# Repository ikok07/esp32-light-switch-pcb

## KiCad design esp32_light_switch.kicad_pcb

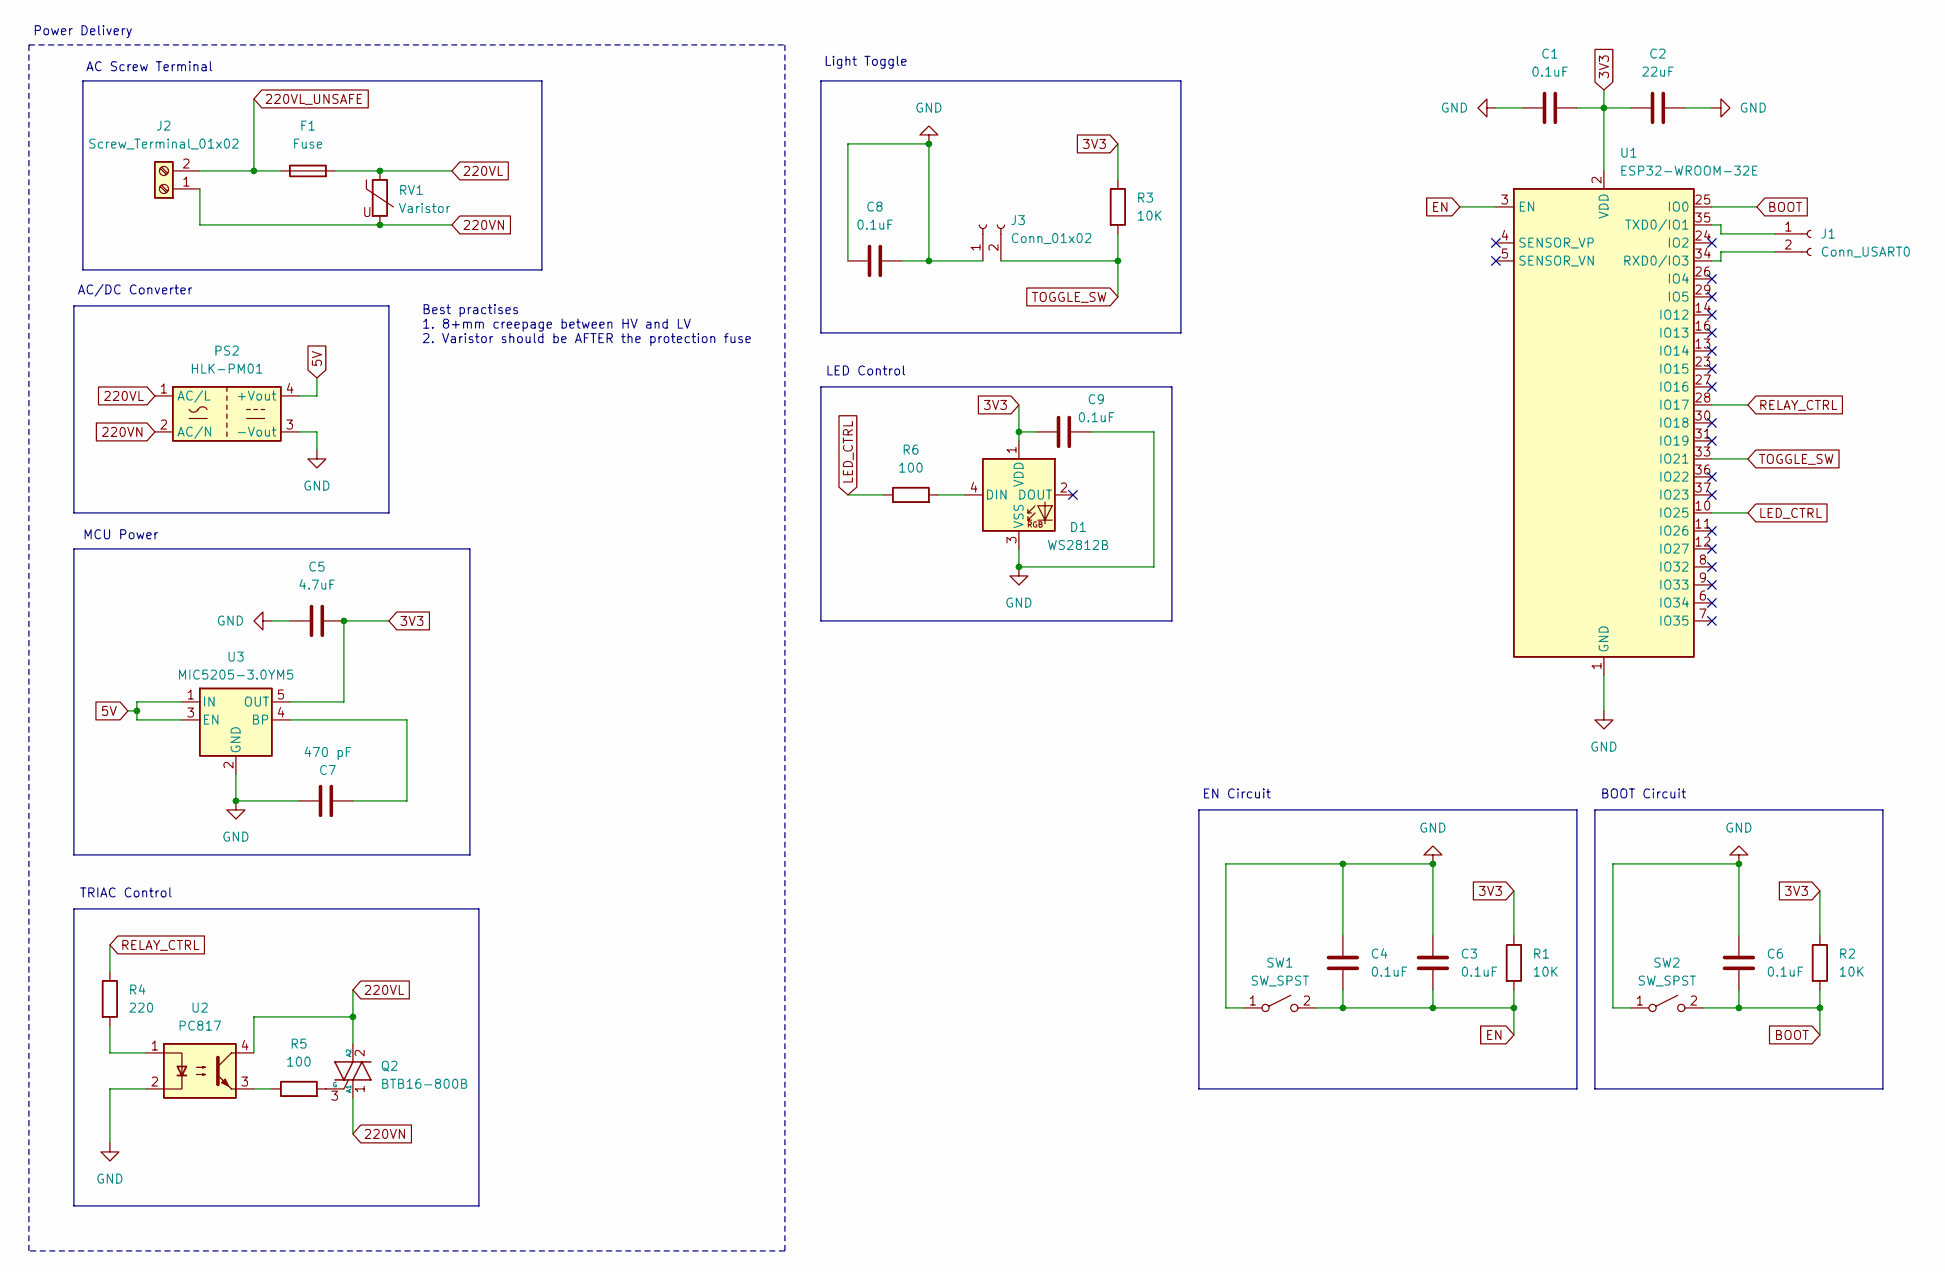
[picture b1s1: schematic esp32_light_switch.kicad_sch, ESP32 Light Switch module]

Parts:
C1, C3, C4, C6, C8, C9: 0.1uF; C_0805_2012Metric_Pad1.18x1.45mm_HandSolder
C2: 22uF; C_0805_2012Metric_Pad1.18x1.45mm_HandSolder
C5: 4.7uF; CP_EIA-6032-20_AVX-F_HandSolder
C7: 470 pF; C_Disc_D5.0mm_W2.5mm_P5.00mm
D1: WS2812B; LED_WS2812B_PLCC4_5.0x5.0mm_P3.2mm
F1: Fuse; Fuseholder_Cylinder-5x20mm_Schurter_0031_8201_Horizontal_Op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
J1: Conn_USART0; PinHeader_1x02_P2.54mm_Vertical
J2: Screw_Terminal_01x02; DG3065002P1200AH
J3: Conn_01x02; PinHeader_1x02_P2.54mm_Vertical
PS2: HLK-PM01; Converter_ACDC_Hi-Link_HLK-PMxx
Q2: BTB16-800B; TO-220-3_Vertical
R1, R2, R3: 10K; R_0805_2012Metric_Pad1.20x1.40mm_HandSolder
R4: 220; R_0805_2012Metric_Pad1.20x1.40mm_HandSolder
R5, R6: 100; R_0805_2012Metric_Pad1.20x1.40mm_HandSolder
RV1: Varistor; RV_Disc_D12mm_W3.9mm_P7.5mm
SW1, SW2: SW_SPST; SW_TH_Tactile_Omron_B3F-100x
U1: ESP32-WROOM-32E; ESP32-WROOM-32D
U2: PC817; DIP-4_W7.62mm_SMDSocket_SmallPads
U3: MIC5205-3.0YM5; SOT-23-5

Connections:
3V3: C1.2, C2.1, C5.2, C9.1, D1.1 (VDD), R1.1, R2.1, R3.1, U1.2 (VDD), U3.5 (OUT)
5V: PS2.4 (+Vout), U3.1 (IN), U3.3 (EN)
220VL: F1.2, PS2.1 (AC/L), Q2.2 (A2), RV1.1, U2.4
220VL_UNSAFE: F1.1, J2.2
220VN: J2.1, PS2.2 (AC/N), Q2.1 (A1), RV1.2
BOOT: C6.1, R2.2, SW2.2 (B), U1.25 (IO0)
EN: C3.1, C4.2, R1.2, SW1.2 (B), U1.3 (EN)
GND: C1.1, C2.2, C3.2, C4.1, C5.1, C6.2, C7.2, C8.1, C8.2, C9.2, D1.3 (VSS), J3.1, PS2.3 (-Vout), SW1.1 (A), SW2.1 (A), U1.1 (GND), U1.15 (GND), U1.38 (GND), U1.39 (GND), U2.2, U3.2 (GND)
LED_CTRL: R6.1, U1.10 (IO25)
unnamed: D1.4 (DIN), R6.2
unnamed: J1.1, U1.35 (TXD0/IO1)
unnamed: J1.2, U1.34 (RXD0/IO3)
unnamed: Q2.3 (G), R5.2
unnamed: R4.2, U2.1
unnamed: R5.1, U2.3
unnamed: C7.1, U3.4 (BP)
RELAY_CTRL: R4.1, U1.28 (IO17)
TOGGLE_SW: J3.2, R3.2, U1.33 (IO21)

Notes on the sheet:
TRIAC Control
Best practises 1. 8+mm creepage between HV and LV 2. Varistor should be AFTER the protection fuse
Light Toggle
AC Screw Terminal
Power Delivery
LED Control
AC/DC Converter
BOOT Circuit
MCU Power
EN Circuit

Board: 2 copper layers, 28 parts (0 on the bottom side), 18 nets, no tracks yet.

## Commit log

2026-02-24 remove temp files
2026-02-25 refactor to use TRIAC and draw initial pcb
